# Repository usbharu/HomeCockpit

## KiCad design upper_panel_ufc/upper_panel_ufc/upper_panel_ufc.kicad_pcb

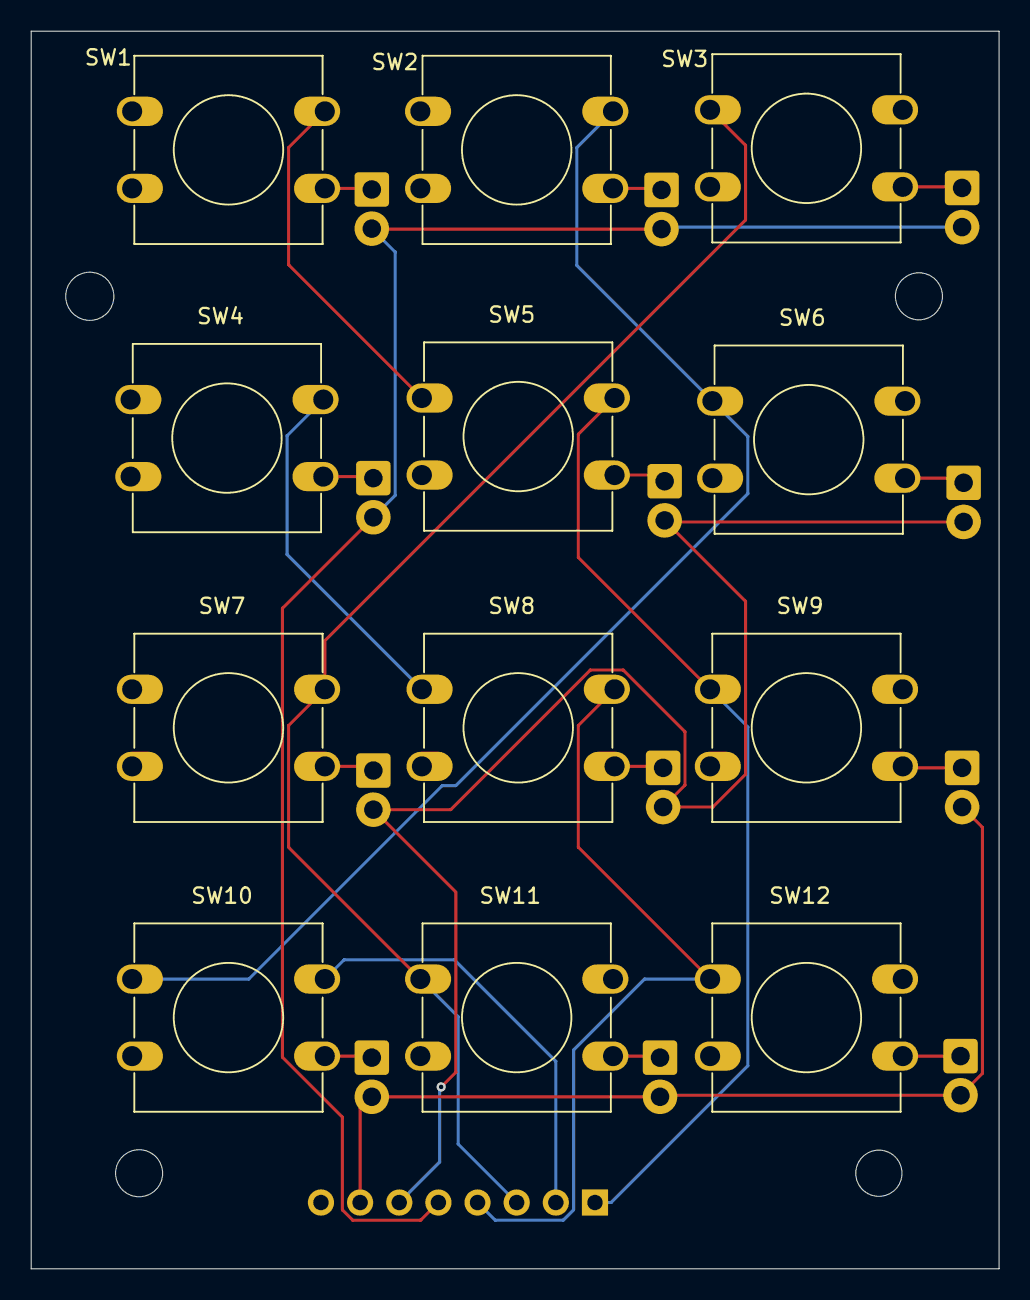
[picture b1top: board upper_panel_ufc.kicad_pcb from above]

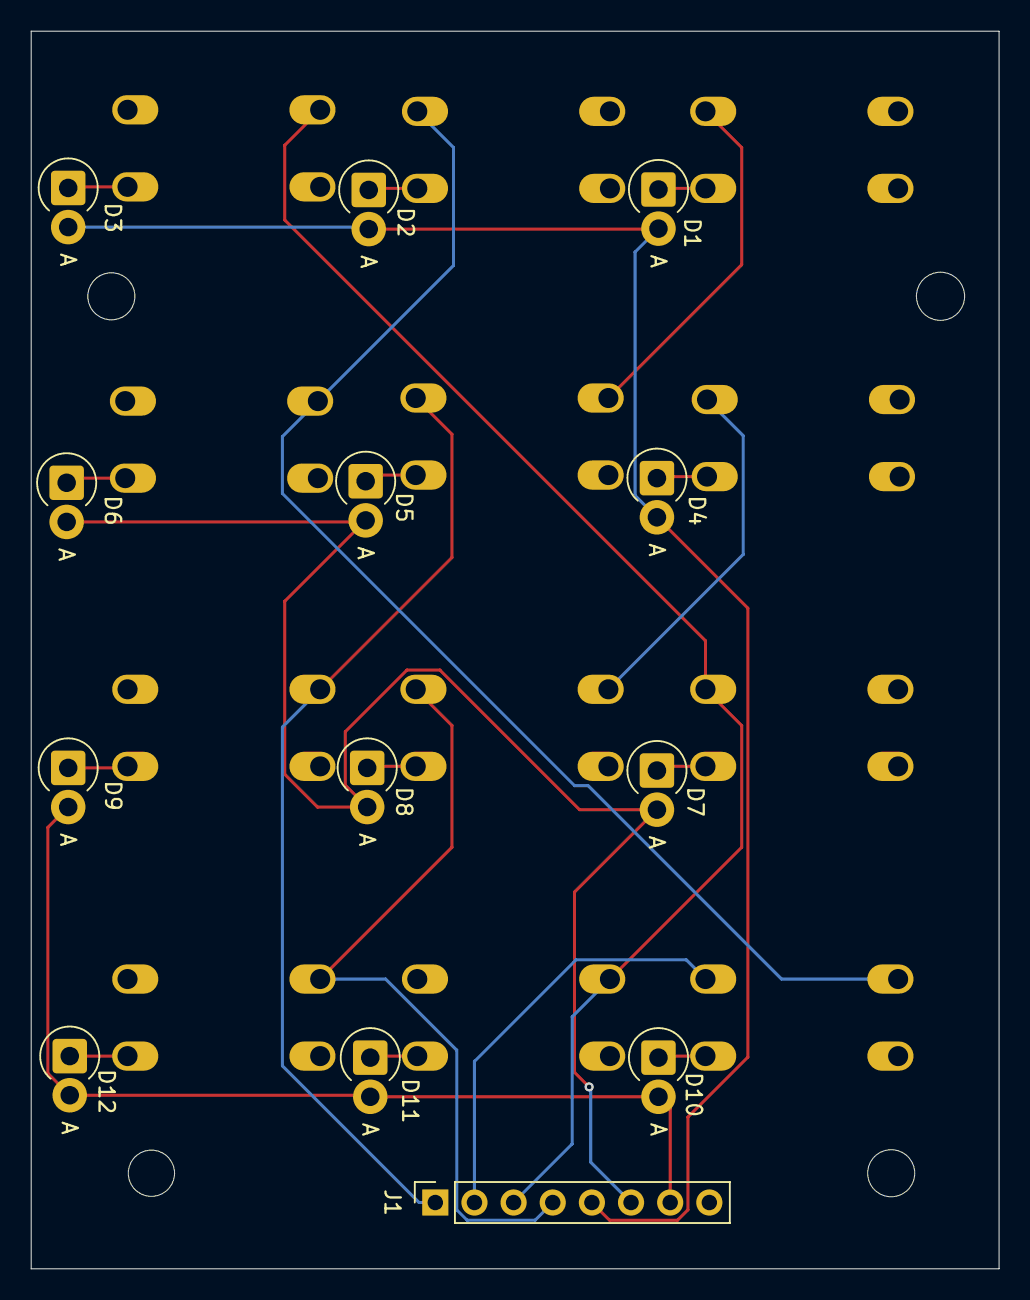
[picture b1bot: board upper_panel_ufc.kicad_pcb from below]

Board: 2 copper layers, 62.8 x 80.3 mm, 25 parts (13 on the bottom side), 19 nets.

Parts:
D1, D2, D3, D4, D5, D6, D7, D8, D9, D10, D11, D12: D; D_DO-15_P2.54mm_Vertical_AnodeUp
J1: Conn_01x08_Pin; PinSocket_1x08_P2.54mm_Vertical
SW1, SW2, SW3, SW4, SW5, SW6, SW7, SW8, SW9, SW10, SW11, SW12: SW_Push; SW_PUSH-12mm-mini

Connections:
unnamed: D1.2 (A), D2.2 (A), D3.2 (A), D4.2 (A), J1.5
unnamed: D1.1 (K), SW1.2
unnamed: D2.1 (K), SW2.2
unnamed: D3.1 (K), SW3.2
unnamed: D4.1 (K), SW4.2
unnamed: D5.2 (A), D6.2 (A), D7.2 (A), D8.2 (A), J1.6
unnamed: D5.1 (K), SW5.2
unnamed: D6.1 (K), SW6.2
unnamed: D7.1 (K), SW7.2
unnamed: D8.1 (K), SW8.2
unnamed: D9.1 (K), SW9.2
unnamed: D9.2 (A), D10.2 (A), D11.2 (A), D12.2 (A), J1.7
unnamed: D10.1 (K), SW10.2
unnamed: D11.1 (K), SW11.2
unnamed: D12.1 (K), SW12.2
unnamed: J1.1, SW1.1, SW5.1, SW9.1
unnamed: J1.2, SW2.1, SW6.1, SW10.1
unnamed: J1.3, SW3.1, SW7.1, SW11.1
unnamed: J1.4, SW4.1, SW8.1, SW12.1

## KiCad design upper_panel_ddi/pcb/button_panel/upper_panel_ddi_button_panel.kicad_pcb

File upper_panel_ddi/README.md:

# Upper Panel DDI

Upper Panel DDI に関する基板設計、機械設計、ファームウェアの対応関係をまとめます。

## 構成

| 対象 | リポジトリ内の場所 | 対応する実装 |
| --- | --- | --- |
| メイン基板 | [`pcb/main_board/`](pcb/main_board/) | [`../firmware/upper_panel_ddi/`](../firmware/upper_panel_ddi/) が搭載MCU上で動作 |
| ボタン基板 | [`pcb/button_panel/`](pcb/button_panel/) | 独立したファームウェアはなく、メイン基板へ接続して使用 |
| ケース・機械部品 | [`mechanical/case/`](mechanical/case/) | メイン基板とボタン基板を組み込む筐体。3Dモデルは将来 `mechanical/case/3d/` に配置 |
| ホスト側モック | [`../utils/upper-panel-ddi-mock/`](../utils/upper-panel-ddi-mock/) | Managerから実機相当のIMCP/HCPデバイスとして利用 |

メイン基板 KiCad プロジェクト: [`pcb/main_board/upper_panel_ddi_main_board.kicad_pro`](pcb/main_board/upper_panel_ddi_main_board.kicad_pro)（回路図のみ。配線は [`firmware/upper_panel_ddi`](../firmware/upper_panel_ddi/) に合わせ、KiCad回路図エディターで `.kicad_sch` を直接編集します）。

メイン基板の `J1`..`J8` は JST 1×6 です。特殊ケーブルで8枚のボタン基板の JST 1×8 に接続します。ケーブルのピン対応は次のとおりです。`ROWn` は各パネルの行番号（0–7）を表します。

| 信号 | メイン基板側 1×6 | ボタン基板側 1×8 |
| --- | --- | --- |
| ROWn | Pin1 | Pin2 |
| COL0 | Pin2 | Pin3 |
| COL1 | Pin3 | Pin4 |
| COL2 | Pin4 | Pin5 |
| COL3 | Pin5 | Pin6 |
| COL4 | Pin6 | Pin7 |

ボタン基板側の Pin1（LED電源）と Pin8（LEDリターン）はメイン基板へ接続しません。Pin2 はスイッチ用ダイオードのアノード共通端子（ROW）です。ボタン基板: [`pcb/button_panel/upper_panel_ddi_button_panel.kicad_pro`](pcb/button_panel/upper_panel_ddi_button_panel.kicad_pro)。

## 検証

CI ではメイン基板に `kicad-cli sch erc`（error 0）、ボタン基板に ERC/DRC を実行します。手順の詳細は [`docs/kicad.md`](../docs/kicad.md) を参照してください。ファームウェアのビルド・書き込みは [`firmware/upper_panel_ddi/README.md`](../firmware/upper_panel_ddi/README.md) を参照してください。

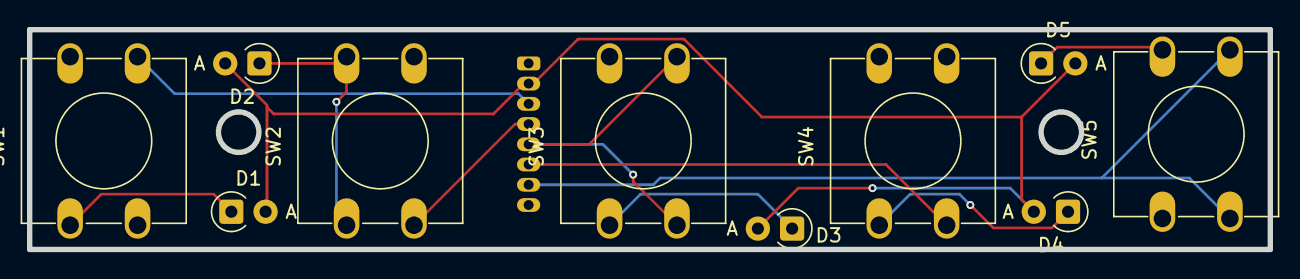
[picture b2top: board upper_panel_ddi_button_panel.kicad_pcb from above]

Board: 2 copper layers, 92.0 x 16.3 mm, 11 parts (1 on the bottom side), 11 nets.

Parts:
D1, D2, D3, D4, D5: D; D_A-405_P2.54mm_Vertical_AnodeUp
J1: Conn_01x08_Pin; JST_ZH_B8B-ZR_1x08_P1.50mm_Vertical
SW1, SW2, SW3, SW4, SW5: SW_Push; SW_PUSH-12mm-mini

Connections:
unnamed: D1.2 (A), D2.2 (A), D3.2 (A), D4.2 (A), D5.2 (A), J1.2
unnamed: D1.1 (K), SW1.1
unnamed: D2.1 (K), SW2.1
unnamed: D3.1 (K), SW3.1
unnamed: D4.1 (K), SW4.1
unnamed: D5.1 (K), SW5.1
unnamed: J1.3, SW1.2
unnamed: J1.4, SW2.2
unnamed: J1.5, SW3.2
unnamed: J1.6, SW4.2
unnamed: J1.7, SW5.2

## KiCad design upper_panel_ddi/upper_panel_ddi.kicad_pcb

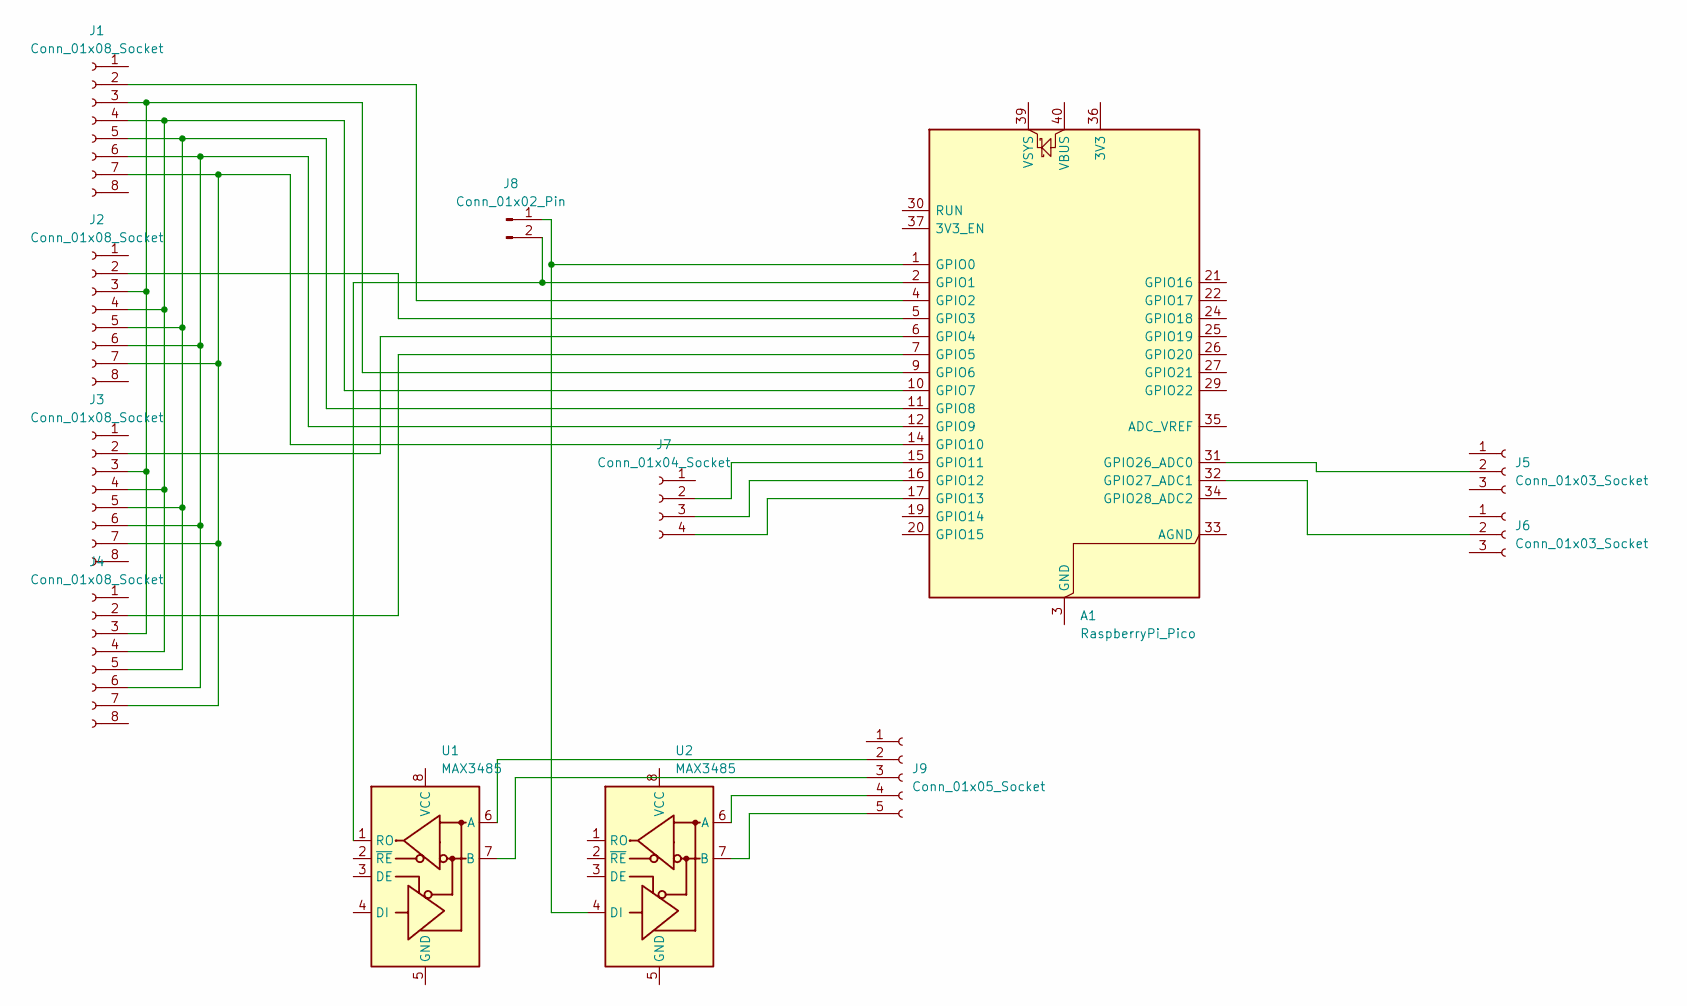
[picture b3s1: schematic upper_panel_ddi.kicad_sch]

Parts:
A1: RaspberryPi_Pico; RaspberryPi_Pico_Common_THT
J1, J2, J3, J4: Conn_01x08_Socket; JST_ZH_B8B-ZR_1x08_P1.50mm_Vertical
J5, J6: Conn_01x03_Socket; JST_ZH_B3B-ZR_1x03_P1.50mm_Vertical
J7: Conn_01x04_Socket; JST_XH_B4B-XH-AM_1x04_P2.50mm_Vertical
J8: Conn_01x02_Pin; PinHeader_1x02_P2.54mm_Vertical
J9: Conn_01x05_Socket; JST_XH_B5B-XH-AM_1x05_P2.50mm_Vertical
U1, U2: MAX3485; SOIC-8_3.9x4.9mm_P1.27mm

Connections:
unnamed: A1.3 (GND), A1.8 (GND), A1.13 (GND), A1.18 (GND), A1.23 (GND), A1.28 (GND), A1.38 (GND)
unnamed: A1.1 (GPIO0), J8.1, U2.4 (DI)
unnamed: A1.2 (GPIO1), J8.2, U1.1 (RO)
unnamed: A1.4 (GPIO2), J1.2
unnamed: A1.5 (GPIO3), J2.2
unnamed: A1.6 (GPIO4), J3.2
unnamed: A1.7 (GPIO5), J4.2
unnamed: A1.9 (GPIO6), J1.3, J2.3, J3.3, J4.3
unnamed: A1.10 (GPIO7), J1.4, J2.4, J3.4, J4.4
unnamed: A1.11 (GPIO8), J1.5, J2.5, J3.5, J4.5
unnamed: A1.12 (GPIO9), J1.6, J2.6, J3.6, J4.6
unnamed: A1.14 (GPIO10), J1.7, J2.7, J3.7, J4.7
unnamed: A1.15 (GPIO11), J7.2
unnamed: A1.16 (GPIO12), J7.3
unnamed: A1.17 (GPIO13), J7.4
unnamed: A1.31 (GPIO26_ADC0), J5.2
unnamed: A1.32 (GPIO27_ADC1), J6.2
unnamed: J9.2, U1.6 (A)
unnamed: J9.3, U1.7 (B)
unnamed: J9.4, U2.6 (A)
unnamed: J9.5, U2.7 (B)

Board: 2 copper layers, 12 parts (2 on the bottom side), 21 nets, no tracks yet.
